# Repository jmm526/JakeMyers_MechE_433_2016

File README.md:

Jake Myers
4/1/16

This is my repository for MechE 433, and will include individual folders for each homework assignment

Extra Line

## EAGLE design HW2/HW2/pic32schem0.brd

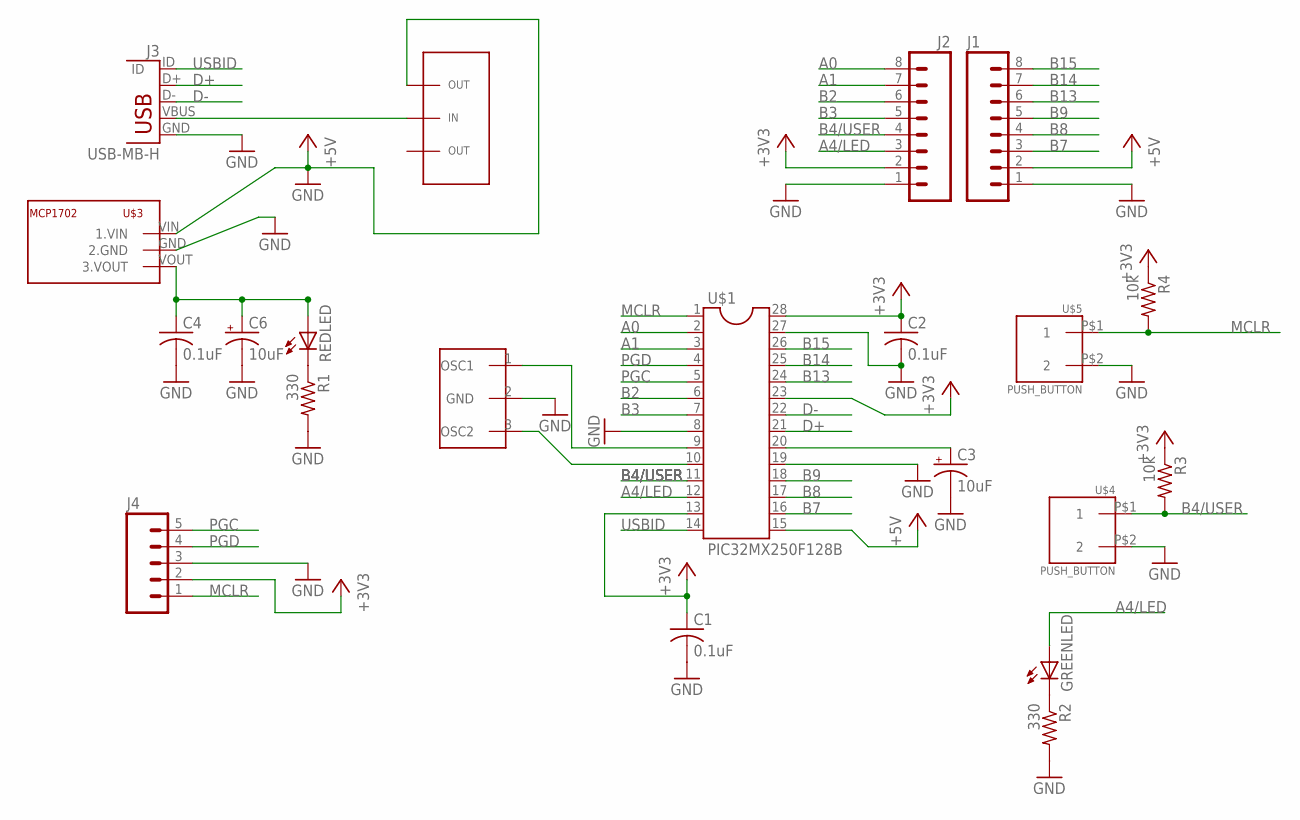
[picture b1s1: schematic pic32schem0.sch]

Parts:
C1, C2, C4: 0.1uF; C025-025X050
C3, C6: 10uF; B45181A
GREENLED: LED3MM
J1, J2: M08; 1X08_ROUND
J3: USB-MB-H
J4: M05PTH; 1X05
R1, R2: 330; 0207/10
R3, R4: 10k; 0207/10
REDLED: LED3MM
U$1: PIC32MX250F128B; DIL28-3
U$2: SLIDE_SWITCH
U$3: MCP1702; TO92
U$4, U$5: PUSH_BUTTON
Y1: RESONATOR; RESONATOR-PTH

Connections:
+3V3: C1.1, C2.1, J2.2, J4.2, R3.1, R4.1, U$1.23 (23.VUSB3V3), U$1.28 (28.AVDD)
+5V: J1.2, U$1.15 (15.VBUS)
A0: J2.8, U$1.2 (2.PGED3/VREF+/CVREF+/AN0/C3INC/RPA0/CTE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)
A1: J2.7, U$1.3 (3.PGED3/VREF-/CVREF-/AN1/RPA1/CTED2/PMD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)
A4/LED: GREENLED.A, J2.3, U$1.12 (12.SOSCO/RPA4/T1CK/CTED9/PMA1/RA4)
B2: J2.6, U$1.6 (6.AN4/C1INB/C2IND/RPB2/SDA2/CTED13/PMD2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)
B3: J2.5, U$1.7 (7.AN5/C1INA/C2INC/RTCC/RPB3/SCL2/PMWR/R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)
B4/USER: J2.4, R3.2, U$1.11 (11.SOSCI/RPB4/RB4), U$4.P$1 (1)
B7: J1.3, U$1.16 (16.TDI/RPB7/CTED3/PMD5/INT0/RB7)
B8: J1.4, U$1.17 (17.TCK/RPB7/CTED10/PMD4/RB8)
B9: J1.5, U$1.18 (18.TDO/RPB9/SDA1/CTED4/PMD3/RB9)
B13: J1.6, U$1.24 (24.AN11/RPB13/CTPLS/PMRD/RB13)
B14: J1.7, U$1.25 (25.CVREFOUT/AN10/C3INB/RPB14/VBUSON/SCK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)
B15: J1.8, U$1.26 (26.AN9/C3INA/RPB15/SCK2/CTED6/PMCS1/RB15)
D+: J3.D+, U$1.21 (21.PGED2/RPB10/D+/CTED11/RB10)
D-: J3.D-, U$1.22 (22.PGEC2/RPB11/D-/RB11)
GND: C1.2, C2.2, C3.-, C4.2, C6.-, J1.1, J2.1, J3.GND, J4.3, R1.2, R2.2, U$1.8 (8.VSS), U$1.19 (19.VSS), U$1.27 (27.AVSS), U$2.4.OUT (3.OUT), U$3.GND (2.GND), U$3.VIN (1.VIN), U$4.P$2 (2), U$5.P$2 (2), Y1.2 (GND)
MCLR: J4.1, R4.2, U$1.1 (1.MCLR_BAR), U$5.P$1 (1)
unnamed: U$1.10 (10.OSC2/CLKO/RPA3/PMA0/RA3), Y1.3 (OSC2)
unnamed: U$1.9 (9.OSC1/SLKI/RPA2/RA2), Y1.1 (OSC1)
unnamed: R1.1, REDLED.K (C)
unnamed: J3.VBUS, U$2.3.IN (2.IN)
unnamed: C4.1, C6.+, REDLED.A, U$3.VOUT (3.VOUT)
unnamed: GREENLED.K (C), R2.1
unnamed: C3.+, U$1.20 (20.VCAP)
PGC: J4.5, U$1.5 (5.PGEC1/AN3/C1INC/C2INA/RPB1/CTED12/PMD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)
PGD: J4.4, U$1.4 (4.PGED1/AN2/C1IND/C2INB/C3IND/RPB0/PMD0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)
USBID: J3.ID, U$1.14 (14.TMS/RPB5/USBID/RB5)

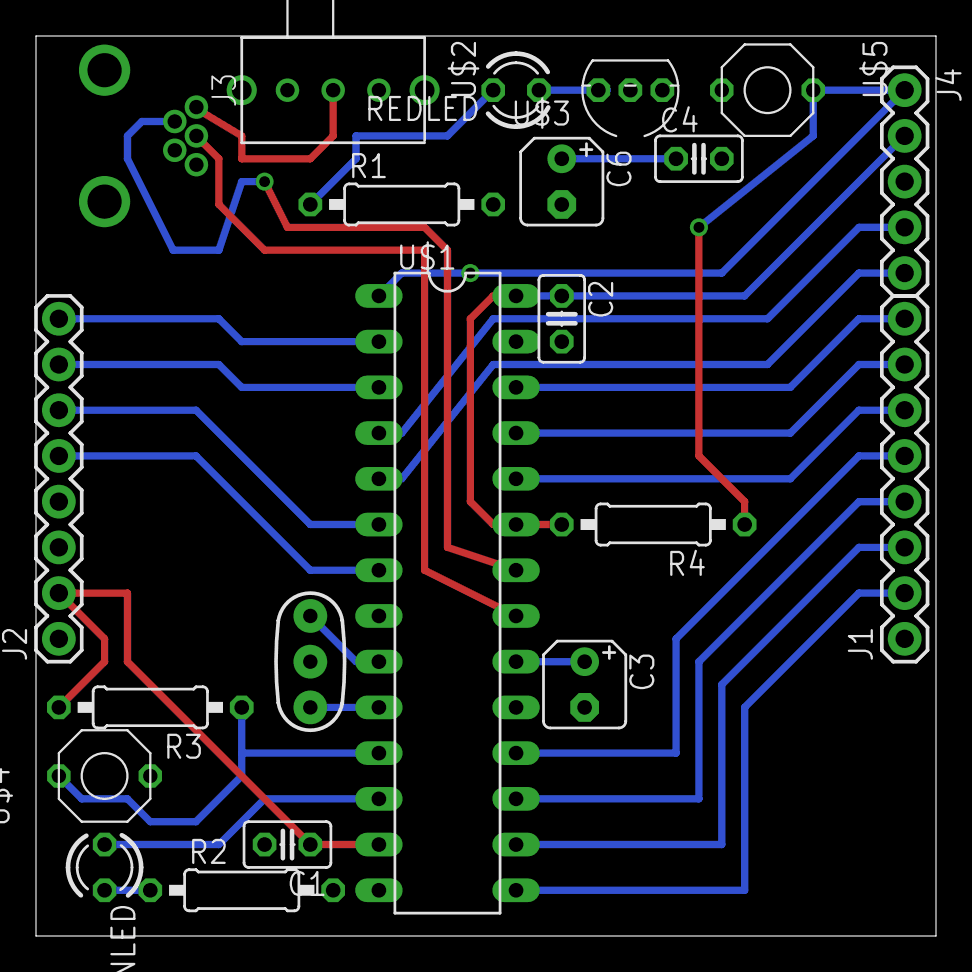
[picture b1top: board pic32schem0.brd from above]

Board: 2 copper layers, 50.0 x 50.0 mm, 21 parts (0 on the bottom side), 28 nets.

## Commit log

2016-04-06 :neckbeard: Added .gitattributes & .gitignore files
2016-04-06 Added ReadMe
2016-04-06 Extra Line
2016-04-06 Added source files through MPLAB IDE
2016-04-06 Added template to main
2016-04-06 Filled in pragma parameters
2016-04-07 Added picture of circuit, Got light flashing i/o code working
2016-04-07 Added HW1 stuff to HW1 folder
2016-04-07 Added HW2
2016-04-07 Created Eagle Project
2016-04-14 Finished Library
2016-04-14 App. halfway done with schematic
2016-04-14 Finished schematic
2016-04-14 Added library iterations to folder inside hw folder
    Important note - The project is still drawing the library from the
    folder in my c:/Eagle...., therefore I will have to manually transfer
    changes made to the library to the hw folder for github to see it
2016-04-14 Finished first draft of board
2016-04-14 Scrapped original pcb, got ground plane to work
2016-04-14 Finished pcb, quite a few errors
2016-04-14 Saved gerber files, havent checked anything yet but likely there are issues
2016-05-25 HW9 added and completed
2016-05-25 HW10 started and completed
    Wheel CAD
2016-05-25 added screenshot for hw10
2016-05-25 HW12 started
2016-06-04 hw12 done
2016-06-04 changed to 500 for better tracking
2016-06-04 hw13 done
2016-06-05 Created base for the android cdc app
2016-06-05 Got cdc app to recognize the pic, but cant read any data from it
